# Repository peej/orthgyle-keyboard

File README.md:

# Orthgyle - Ortholinear keyboard PCB for the Argyle

Orthgyle is a 5x15 ortholinear PCB using through-hole components for the [Argyle keyboard](https://geekhack.org/index.php?topic=116274).

* Designed to be a drop in replacement for the standard staggered Argyle PCB.
* Same Atmega283p MCU and side panel LEDs
* Uses a [Japanese Matrix](https://kbd.news/The-Japanese-duplex-matrix-1391.html) instead of an IO expander to simplify components and firmware.

See the [Bill of materials](BOM.md) for a detailed list of the required parts.

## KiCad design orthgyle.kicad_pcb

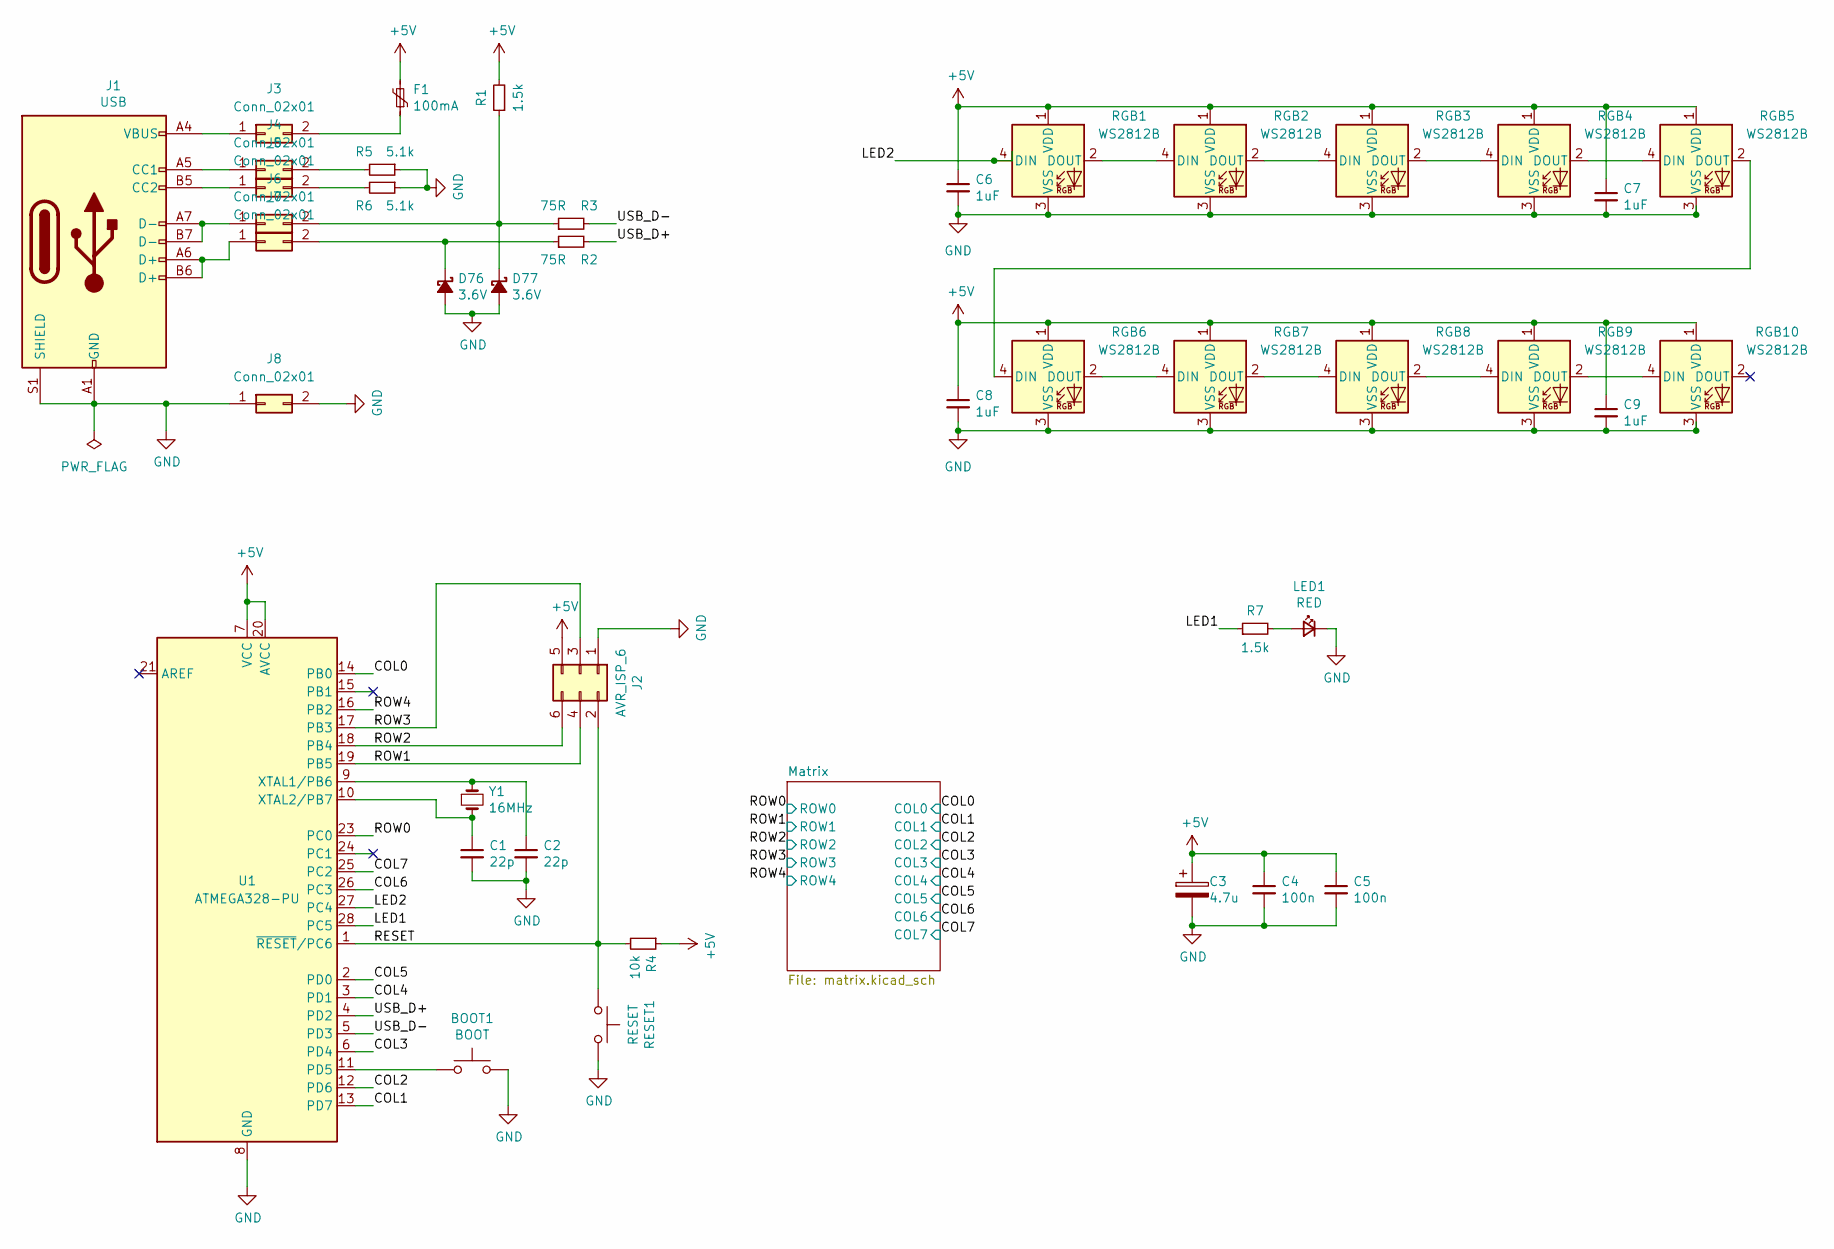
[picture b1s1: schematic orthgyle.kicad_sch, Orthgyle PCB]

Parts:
BOOT1: BOOT; SolderJumper-2_P1.3mm_Open_RoundedPad1.0x1.5mm
C1, C2: 22p; C_Disc_D3.0mm_W1.6mm_P2.50mm
C3: 4.7u; CP_Radial_D4.0mm_P1.50mm
C4, C5: 100n; C_Disc_D4.3mm_W1.9mm_P5.00mm
C6, C7, C8, C9: 1uF; C_Disc_D4.3mm_W1.9mm_P5.00mm
D76, D77: 3.6V; D_DO-35_SOD27_P7.62mm_Horizontal
F1: 100mA; Fuse_Bourns_MF-RHT100
J1: USB; USB_C_Receptacle_HRO_TYPE-C-31-M-12
J2: AVR_ISP_6; PinHeader_2x03_P2.54mm_Vertical
J3, J4, J5, J6, J7, J8: Conn_02x01; SolderJumper-2_P1.3mm_Bridged_RoundedPad1.0x1.5mm
LED1: RED; LED_D3.0mm
R1, R7: 1.5k; R_Axial_DIN0204_L3.6mm_D1.6mm_P7.62mm_Horizontal
R2, R3: 75R; R_Axial_DIN0204_L3.6mm_D1.6mm_P7.62mm_Horizontal
R4: 10k; R_Axial_DIN0204_L3.6mm_D1.6mm_P7.62mm_Horizontal
R5, R6: 5.1k; R_Axial_DIN0204_L3.6mm_D1.6mm_P7.62mm_Horizontal
RESET1: RESET; SolderJumper-2_P1.3mm_Open_RoundedPad1.0x1.5mm
RGB1, RGB2, RGB3, RGB4, RGB5, RGB6, RGB7, RGB8, RGB9, RGB10: WS2812B; SK6812-MINI-E
U1: ATMEGA328-PU; DIP-28_W7.62mm
Y1: 16MHz; Crystal_HC49-4H_Vertical

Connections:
+5V: C3.1, C4.1, C5.1, C6.1, C7.1, C8.1, C9.1, F1.2, J2.5, R1.2, R4.1, RGB1.1 (VDD), RGB2.1 (VDD), RGB3.1 (VDD), RGB4.1 (VDD), RGB5.1 (VDD), RGB6.1 (VDD), RGB7.1 (VDD), RGB8.1 (VDD), RGB9.1 (VDD), RGB10.1 (VDD), U1.7 (VCC), U1.20 (AVCC)
/COL0: U1.14 (PB0); also elsewhere on the board
/COL1: U1.13 (PD7); also elsewhere on the board
/COL2: U1.12 (PD6); also elsewhere on the board
/COL3: U1.6 (PD4); also elsewhere on the board
/COL4: U1.3 (PD1); also elsewhere on the board
/COL5: U1.2 (PD0); also elsewhere on the board
/COL6: U1.26 (PC3); also elsewhere on the board
/COL7: U1.25 (PC2); also elsewhere on the board
/LED1: R7.1, U1.28 (PC5)
/LED2: RGB1.4 (DIN), U1.27 (PC4)
/RESET: J2.2, R4.2, RESET1.1, U1.1 (~RESET/PC6)
/ROW0: U1.23 (PC0); also elsewhere on the board
/ROW1: J2.4, U1.19 (PB5); also elsewhere on the board
/ROW2: J2.6, U1.18 (PB4); also elsewhere on the board
/ROW3: J2.3, U1.17 (PB3); also elsewhere on the board
/ROW4: U1.16 (PB2); also elsewhere on the board
/USB_D+: R2.2, U1.4 (PD2)
/USB_D-: R3.2, U1.5 (PD3)
GND: BOOT1.2, C1.2, C2.2, C3.2, C4.2, C5.2, C6.2, C7.2, C8.2, C9.2, D76.2 (A), D77.2 (A), J1.A1 (GND), J1.A12 (GND), J1.B1 (GND), J1.B12 (GND), J1.S1 (SHIELD), J2.1, J8.1, J8.2, LED1.1 (K), R5.1, R6.1, RESET1.2, RGB1.3 (VSS), RGB2.3 (VSS), RGB3.3 (VSS), RGB4.3 (VSS), RGB5.3 (VSS), RGB6.3 (VSS), RGB7.3 (VSS), RGB8.3 (VSS), RGB9.3 (VSS), RGB10.3 (VSS), U1.8 (GND), U1.22 (GND)
unnamed: D76.1 (K), J7.2, R2.1
unnamed: D77.1 (K), J6.2, R1.1, R3.1
unnamed: J1.A5 (CC1), J4.1
unnamed: J1.B5 (CC2), J5.1
unnamed: J1.A4 (VBUS), J1.A9 (VBUS), J1.B4 (VBUS), J1.B9 (VBUS), J3.1
unnamed: F1.1, J3.2
unnamed: J4.2, R5.2
unnamed: J5.2, R6.2
unnamed: J1.A7 (D-), J1.B7 (D-), J6.1
unnamed: J1.A6 (D+), J1.B6 (D+), J7.1
unnamed: LED1.2 (A), R7.2
unnamed: RGB1.2 (DOUT), RGB2.4 (DIN)
unnamed: RGB2.2 (DOUT), RGB3.4 (DIN)
unnamed: RGB3.2 (DOUT), RGB4.4 (DIN)
unnamed: RGB4.2 (DOUT), RGB5.4 (DIN)
unnamed: RGB5.2 (DOUT), RGB6.4 (DIN)
unnamed: RGB6.2 (DOUT), RGB7.4 (DIN)
unnamed: RGB7.2 (DOUT), RGB8.4 (DIN)
unnamed: RGB8.2 (DOUT), RGB9.4 (DIN)
unnamed: RGB9.2 (DOUT), RGB10.4 (DIN)
unnamed: BOOT1.1, U1.11 (PD5)
unnamed: C2.1, U1.9 (XTAL1/PB6), Y1.1
unnamed: C1.1, U1.10 (XTAL2/PB7), Y1.2

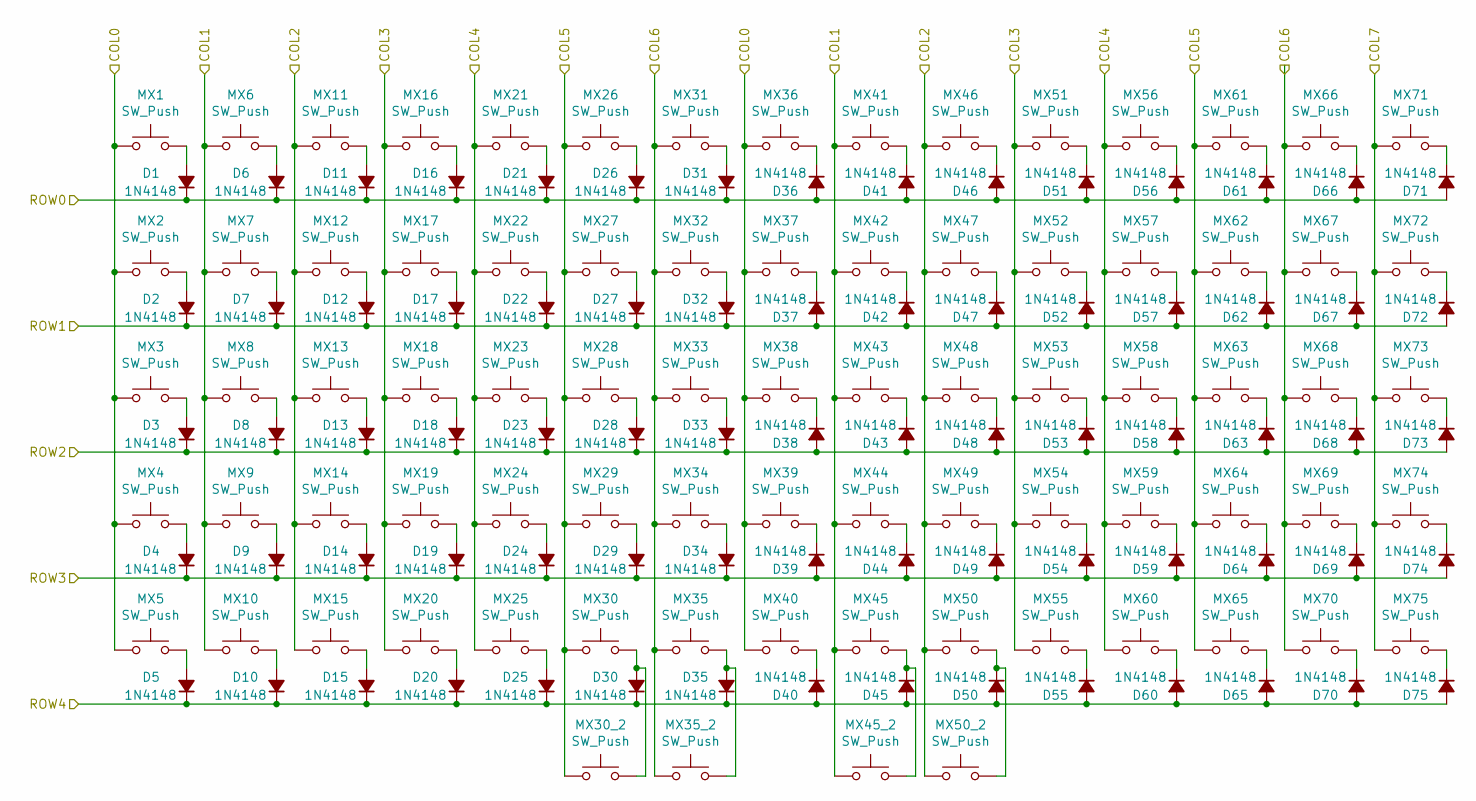
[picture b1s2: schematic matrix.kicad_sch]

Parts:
D1, D2, D3, D4, D5, D6, D7, D8, D9, D10, D11, D12, D13, D14, D15, D16, D17, D18, D19, D20, D21, D22, D23, D24, D25, D26, D27, D28, D29, D30, D31, D32, D33, D34, D35, D36, D37, D38, D39, D40, D41, D42, D43, D44, D45, D46, D47, D48, D49, D50, D51, D52, D53, D54, D55, D56, D57, D58, D59, D60, D61, D62, D63, D64, D65, D66, D67, D68, D69, D70, D71, D72, D73, D74, D75: 1N4148; D_DO-35_SOD27_P7.62mm_Horizontal
MX1, MX2, MX3, MX4, MX5, MX6, MX7, MX8, MX9, MX10, MX11, MX12, MX13, MX14, MX15, MX16, MX17, MX18, MX19, MX20, MX21, MX22, MX23, MX24, MX25, MX26, MX27, MX28, MX29, MX30, MX31, MX32, MX33, MX34, MX35, MX36, MX37, MX38, MX39, MX41, MX42, MX43, MX44, MX45, MX46, MX47, MX48, MX49, MX50, MX51, MX52, MX53, MX54, MX55, MX56, MX57, MX58, MX59, MX60, MX61, MX62, MX63, MX64, MX65, MX66, MX67, MX68, MX69, MX70, MX71, MX72, MX73, MX74, MX75: SW_Push; MX
MX30_2, MX35_2, MX45_2, MX50_2: SW_Push; MX_PCB_200H
MX40: SW_Push; MX_PCB_700H

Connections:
/COL0: MX1.2, MX2.2, MX3.2, MX4.2, MX5.2, MX36.2, MX37.2, MX38.2, MX39.2, MX40.2; also elsewhere on the board
/COL1: MX6.2, MX7.2, MX8.2, MX9.2, MX10.2, MX41.2, MX42.2, MX43.2, MX44.2, MX45.2, MX45_2.2; also elsewhere on the board
/COL2: MX11.2, MX12.2, MX13.2, MX14.2, MX15.2, MX46.2, MX47.2, MX48.2, MX49.2, MX50.2, MX50_2.2; also elsewhere on the board
/COL3: MX16.2, MX17.2, MX18.2, MX19.2, MX20.2, MX51.2, MX52.2, MX53.2, MX54.2, MX55.2; also elsewhere on the board
/COL4: MX21.2, MX22.2, MX23.2, MX24.2, MX25.2, MX56.2, MX57.2, MX58.2, MX59.2, MX60.2; also elsewhere on the board
/COL5: MX26.2, MX27.2, MX28.2, MX29.2, MX30.2, MX30_2.2, MX61.2, MX62.2, MX63.2, MX64.2, MX65.2; also elsewhere on the board
/COL6: MX31.2, MX32.2, MX33.2, MX34.2, MX35.2, MX35_2.2, MX66.2, MX67.2, MX68.2, MX69.2, MX70.2; also elsewhere on the board
/COL7: MX71.2, MX72.2, MX73.2, MX74.2, MX75.2; also elsewhere on the board
/ROW0: D1.1 (K), D6.1 (K), D11.1 (K), D16.1 (K), D21.1 (K), D26.1 (K), D31.1 (K), D36.2 (A), D41.2 (A), D46.2 (A), D51.2 (A), D56.2 (A), D61.2 (A), D66.2 (A), D71.2 (A); also elsewhere on the board
/ROW1: D2.1 (K), D7.1 (K), D12.1 (K), D17.1 (K), D22.1 (K), D27.1 (K), D32.1 (K), D37.2 (A), D42.2 (A), D47.2 (A), D52.2 (A), D57.2 (A), D62.2 (A), D67.2 (A), D72.2 (A); also elsewhere on the board
/ROW2: D3.1 (K), D8.1 (K), D13.1 (K), D18.1 (K), D23.1 (K), D28.1 (K), D33.1 (K), D38.2 (A), D43.2 (A), D48.2 (A), D53.2 (A), D58.2 (A), D63.2 (A), D68.2 (A), D73.2 (A); also elsewhere on the board
/ROW3: D4.1 (K), D9.1 (K), D14.1 (K), D19.1 (K), D24.1 (K), D29.1 (K), D34.1 (K), D39.2 (A), D44.2 (A), D49.2 (A), D54.2 (A), D59.2 (A), D64.2 (A), D69.2 (A), D74.2 (A); also elsewhere on the board
/ROW4: D5.1 (K), D10.1 (K), D15.1 (K), D20.1 (K), D25.1 (K), D30.1 (K), D35.1 (K), D40.2 (A), D45.2 (A), D50.2 (A), D55.2 (A), D60.2 (A), D65.2 (A), D70.2 (A), D75.2 (A); also elsewhere on the board
unnamed: D1.2 (A), MX1.1
unnamed: D2.2 (A), MX2.1
unnamed: D3.2 (A), MX3.1
unnamed: D4.2 (A), MX4.1
unnamed: D5.2 (A), MX5.1
unnamed: D6.2 (A), MX6.1
unnamed: D7.2 (A), MX7.1
unnamed: D8.2 (A), MX8.1
unnamed: D9.2 (A), MX9.1
unnamed: D10.2 (A), MX10.1
unnamed: D11.2 (A), MX11.1
unnamed: D12.2 (A), MX12.1
unnamed: D13.2 (A), MX13.1
unnamed: D14.2 (A), MX14.1
unnamed: D15.2 (A), MX15.1
unnamed: D16.2 (A), MX16.1
unnamed: D17.2 (A), MX17.1
unnamed: D18.2 (A), MX18.1
unnamed: D19.2 (A), MX19.1
unnamed: D20.2 (A), MX20.1
unnamed: D21.2 (A), MX21.1
unnamed: D22.2 (A), MX22.1
unnamed: D23.2 (A), MX23.1
unnamed: D24.2 (A), MX24.1
unnamed: D25.2 (A), MX25.1
unnamed: D26.2 (A), MX26.1
unnamed: D27.2 (A), MX27.1
unnamed: D28.2 (A), MX28.1
unnamed: D29.2 (A), MX29.1
unnamed: D30.2 (A), MX30.1, MX30_2.1
unnamed: D31.2 (A), MX31.1
unnamed: D32.2 (A), MX32.1
unnamed: D33.2 (A), MX33.1
unnamed: D34.2 (A), MX34.1
unnamed: D35.2 (A), MX35.1, MX35_2.1
unnamed: D36.1 (K), MX36.1
unnamed: D37.1 (K), MX37.1
unnamed: D38.1 (K), MX38.1
unnamed: D39.1 (K), MX39.1
unnamed: D40.1 (K), MX40.1
unnamed: D41.1 (K), MX41.1
unnamed: D42.1 (K), MX42.1
unnamed: D43.1 (K), MX43.1
unnamed: D44.1 (K), MX44.1
unnamed: D45.1 (K), MX45.1, MX45_2.1
unnamed: D46.1 (K), MX46.1
unnamed: D47.1 (K), MX47.1
unnamed: D48.1 (K), MX48.1
unnamed: D49.1 (K), MX49.1
unnamed: D50.1 (K), MX50.1, MX50_2.1
unnamed: D51.1 (K), MX51.1
unnamed: D52.1 (K), MX52.1
unnamed: D53.1 (K), MX53.1
unnamed: D54.1 (K), MX54.1
unnamed: D55.1 (K), MX55.1
unnamed: D56.1 (K), MX56.1
unnamed: D57.1 (K), MX57.1
unnamed: D58.1 (K), MX58.1
unnamed: D59.1 (K), MX59.1
unnamed: D60.1 (K), MX60.1
unnamed: D61.1 (K), MX61.1
unnamed: D62.1 (K), MX62.1
unnamed: D63.1 (K), MX63.1
unnamed: D64.1 (K), MX64.1
unnamed: D65.1 (K), MX65.1
unnamed: D66.1 (K), MX66.1
unnamed: D67.1 (K), MX67.1
unnamed: D68.1 (K), MX68.1
unnamed: D69.1 (K), MX69.1
unnamed: D70.1 (K), MX70.1
unnamed: D71.1 (K), MX71.1
unnamed: D72.1 (K), MX72.1
unnamed: D73.1 (K), MX73.1
unnamed: D74.1 (K), MX74.1
unnamed: D75.1 (K), MX75.1

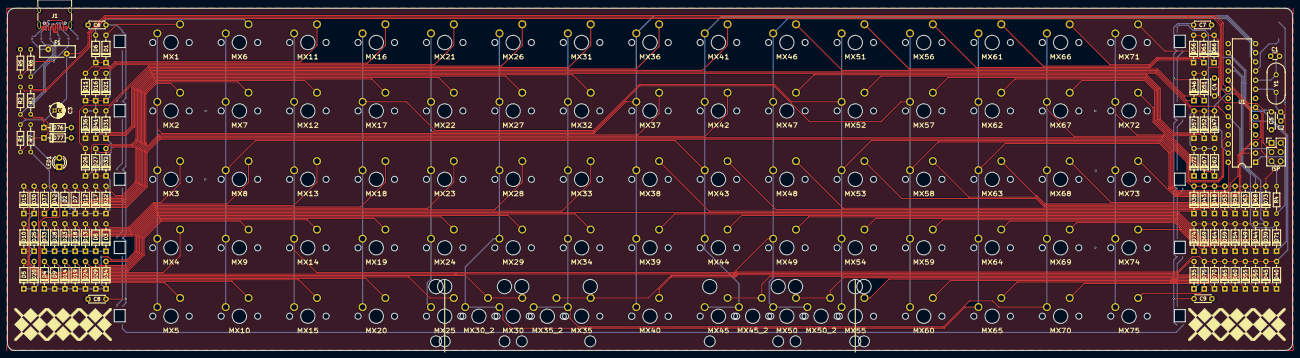
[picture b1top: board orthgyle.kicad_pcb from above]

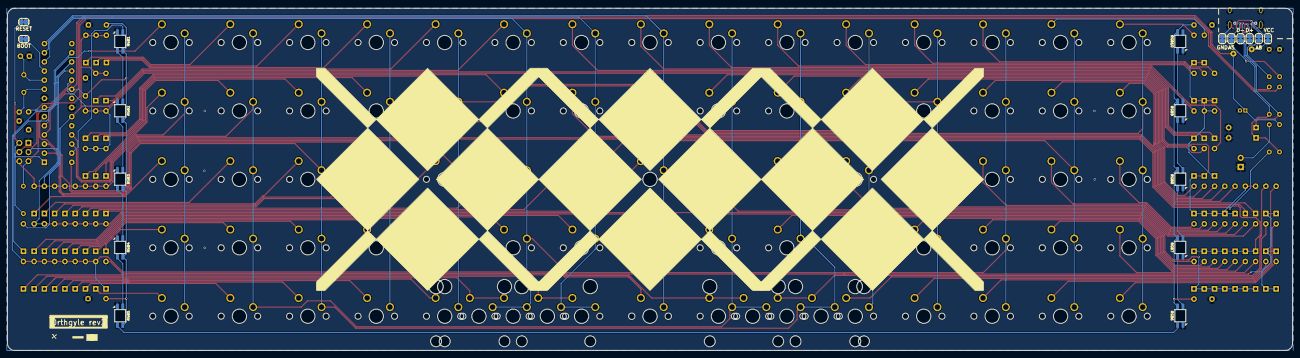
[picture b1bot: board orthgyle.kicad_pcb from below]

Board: 2 copper layers, 357.8 x 95.2 mm, 196 parts (18 on the bottom side), 118 nets.

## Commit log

2024-12-28 Add component files
2024-12-28 Add footprint files
2024-12-28 Add project files
2024-12-28 Add plate project
2024-12-28 Add exported gerbers
2024-12-28 Update PCB page settings
2024-12-28 Add basic README
2024-12-29 Add stab cutouts to plate
2024-12-29 Flip 2u stabilizers
2025-01-04 Move decoupling capacitors closer to ICs
2025-01-05 Rename RGB diodes
2025-01-05 Add BOM
2025-03-13 Update plate file
2025-03-15 Add plate file DXF export
2025-03-15 Update gerbers
2025-03-15 Align USB port with case location
    Switch to SK6812 mini-e LEDs
    Flip stabilizer orientation
2025-03-29 Update BOM and images
2025-03-29 Switch LEDs to SK6812-mini-e
2026-01-21 Add center offset 2u keys
